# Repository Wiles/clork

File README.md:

# clork

One year, one week and one day duration clocks displaying beginning of January a Thursday at 20:50.

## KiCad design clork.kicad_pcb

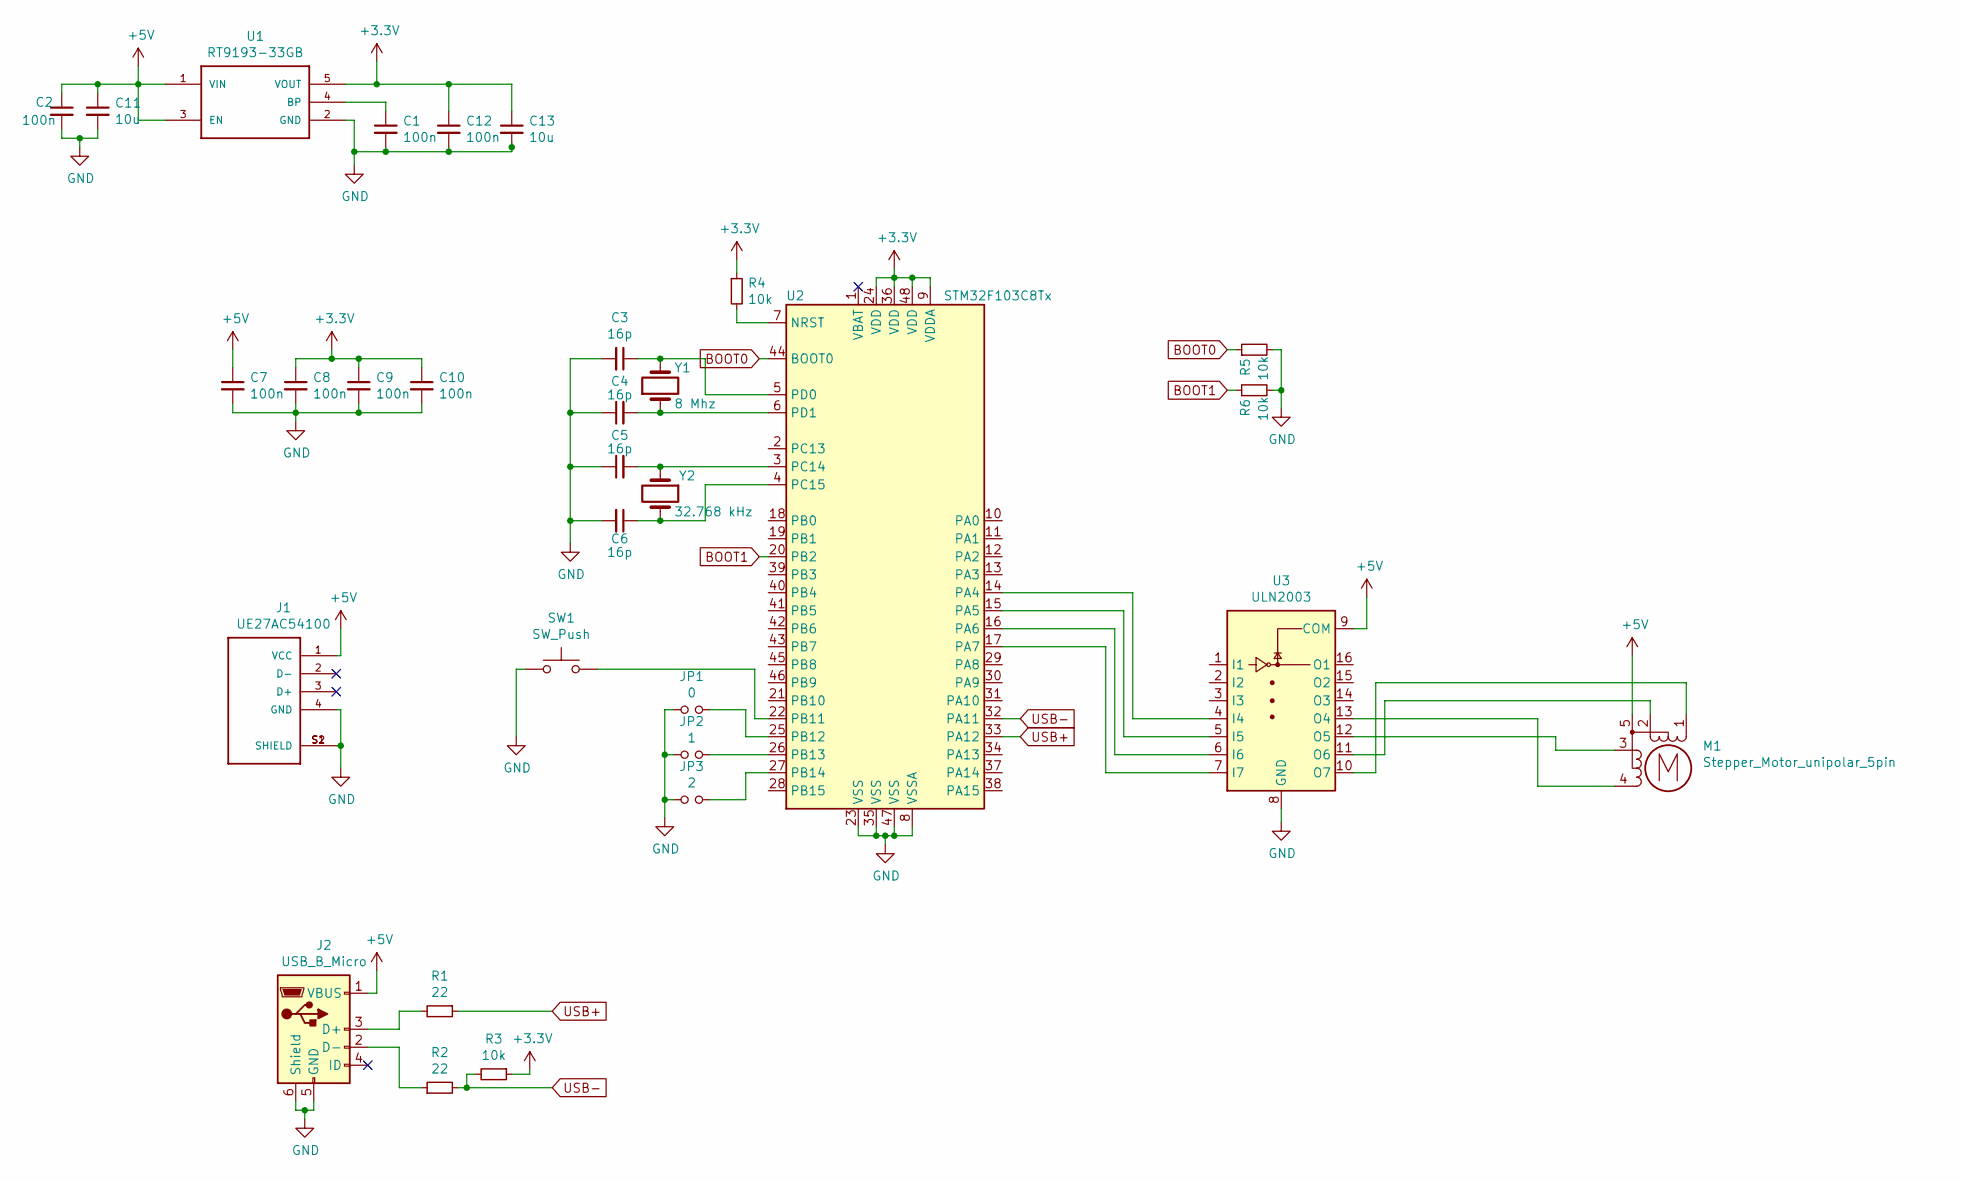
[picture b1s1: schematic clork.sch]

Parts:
C1, C2, C7, C8, C9, C10, C12: 100n; C_0603_1608Metric
C3, C4, C5, C6: 16p; C_0603_1608Metric
C11, C13: 10u; C_0805_2012Metric
J1: UE27AC54100; AMPHENOL_UE27AC54100
J2: USB_B_Micro; USB_Micro-B_Molex_47346-0001
JP1: 0; SolderJumper-2_P1.3mm_Open_Pad1.0x1.5mm
JP2: 1; SolderJumper-2_P1.3mm_Open_Pad1.0x1.5mm
JP3: 2; SolderJumper-2_P1.3mm_Open_Pad1.0x1.5mm
M1: Stepper_Motor_unipolar_5pin; JST_XH_B05B-XH-A_1x05_P2.50mm_Vertical
R1, R2: 22; R_0603_1608Metric
R3, R4, R5, R6: 10k; R_0603_1608Metric
SW1: SW_Push; SW_SPST_PTS645
U1: RT9193-33GB; SOT94P279X129-5N
U2: STM32F103C8Tx; LQFP-48_7x7mm_P0.5mm
U3: ULN2003; SOIC-16_3.9x9.9mm_P1.27mm
Y1: 8 Mhz; Crystal_SMD_Abracon_ABM3-2Pin_5.0x3.2mm
Y2: 32.768 kHz; Crystal_SMD_3215-2Pin_3.2x1.5mm

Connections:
+3V3: C8.1, C9.1, C10.1, C12.1, C13.1, R3.1, R4.1, U1.5 (VOUT), U2.9 (VDDA), U2.24 (VDD), U2.36 (VDD), U2.48 (VDD)
+5V: C2.1, C7.1, C11.1, J1.1 (VCC), J2.1 (VBUS), M1.5, U1.1 (VIN), U1.3 (EN), U3.9 (COM)
BOOT0: R5.1, U2.44 (BOOT0)
BOOT1: R6.1, U2.20 (PB2)
GND: C1.2, C2.2, C3.2, C4.1, C5.1, C6.2, C7.2, C8.2, C9.2, C10.2, C11.2, C12.2, C13.2, J1.4 (GND), J1.S1 (SHIELD), J1.S2 (SHIELD), J2.5 (GND), J2.6 (Shield), JP1.1, JP2.1, JP3.1, R5.2, R6.2, SW1.1, U1.2 (GND), U2.8 (VSSA), U2.23 (VSS), U2.35 (VSS), U2.47 (VSS), U3.8 (GND); also elsewhere on the board
unnamed: C1.1, U1.4 (BP)
unnamed: C3.1, U2.5 (PD0), Y1.2
unnamed: C4.2, U2.6 (PD1), Y1.1
unnamed: C5.2, U2.3 (PC14), Y2.1
unnamed: C6.1, U2.4 (PC15), Y2.2
unnamed: J2.2 (D-), R2.1
unnamed: J2.3 (D+), R1.2
unnamed: JP1.2, U2.25 (PB12)
unnamed: JP2.2, U2.26 (PB13)
unnamed: JP3.2, U2.27 (PB14)
unnamed: M1.1 (-), U3.10 (O7)
unnamed: M1.2, U3.11 (O6)
unnamed: M1.3, U3.12 (O5)
unnamed: M1.4, U3.13 (O4)
unnamed: R4.2, U2.7 (NRST)
unnamed 23: SW1.2, U2.22 (PB11); also elsewhere on the board
unnamed: U2.14 (PA4), U3.4 (I4)
unnamed: U2.15 (PA5), U3.5 (I5)
unnamed: U2.16 (PA6), U3.6 (I6)
unnamed: U2.17 (PA7), U3.7 (I7)
USB+: R1.1, U2.33 (PA12)
USB-: R2.2, R3.2, U2.32 (PA11)

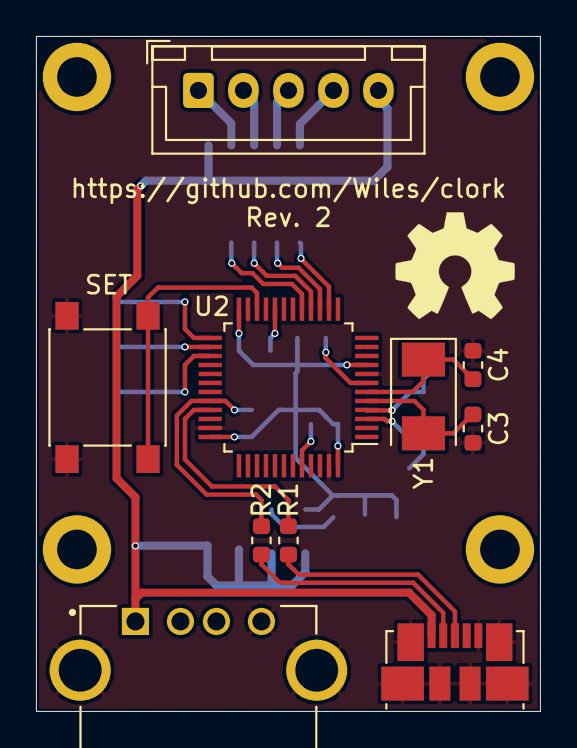
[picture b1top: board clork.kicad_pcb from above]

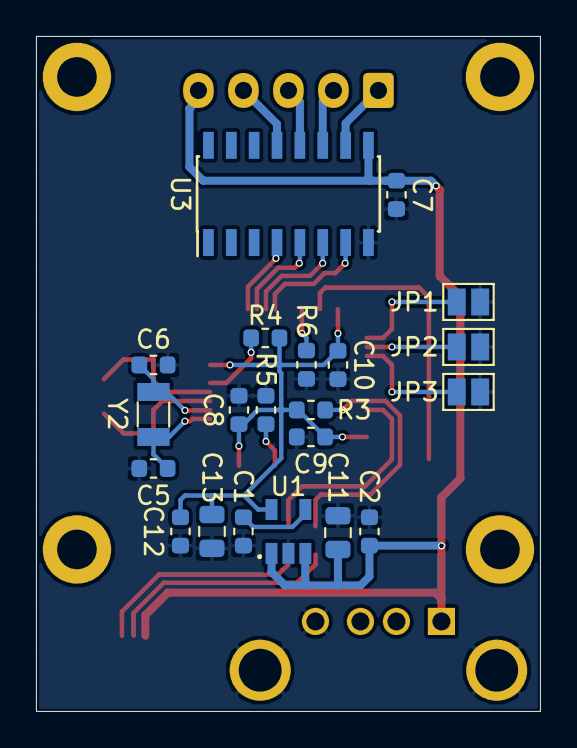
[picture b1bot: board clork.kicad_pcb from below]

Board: 2 copper layers, 28.0 x 37.5 mm, 31 parts (21 on the bottom side), 27 nets.

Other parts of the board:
SET: SW_Push; SW_SPST_PTS645

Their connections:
GND: SET.1; also elsewhere on the board
unnamed 23: SET.2; also elsewhere on the board

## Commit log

2019-12-30 Initial PCB and basic code
2019-12-30 Moved both USBs to bottom of board
2019-12-30 Added gerber files to gitignore
2019-12-30 Added screenshot of arduino board settings
2020-01-01 Added OpenSCAD model of clork face
2020-01-07 Fixed tapping hole sizes
2020-01-07 Fixed PD resistors for BOOT0 and BOOT1
2020-01-07 Added button for setting time
2020-01-23 Fixed reversed USB + and -
2020-01-23 Fixed silkscreen
2020-01-26 Fixed spacing for PCB screw holes
2020-07-24 Added image of project
2020-07-24 Added image to README
2020-07-24 Added time interpretation from clorks.
2020-11-29 Cleaned up face model code
2020-11-29 Added tide labels
2020-11-29 Added moon phases
